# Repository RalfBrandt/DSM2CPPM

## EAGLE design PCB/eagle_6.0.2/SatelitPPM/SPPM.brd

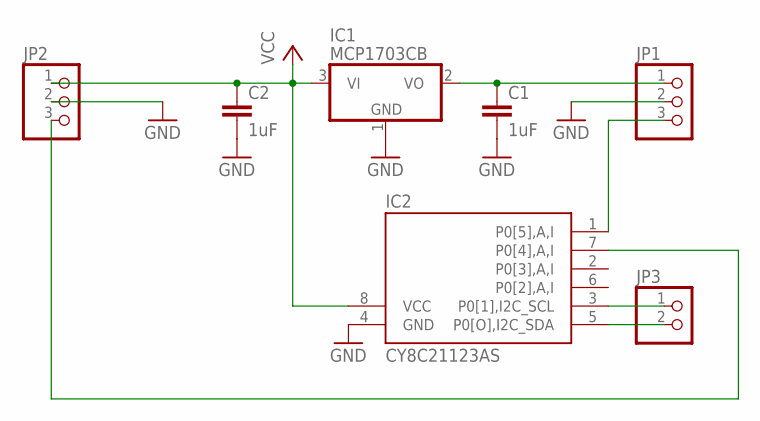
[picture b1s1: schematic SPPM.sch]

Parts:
C1, C2: 1uF; C0805
IC1: MCP1703CB; SOT23
IC2: CY8C21123AS; SOIC8
JP1, JP2: PINHD-1X3; 1X03
JP3: PINHD-1X2; 1X02

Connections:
GND: C1.2, C2.2, IC1.1 (GND), IC2.4 (GND), JP1.2, JP2.2
unnamed: IC2.7 (P0[4],A,I), JP2.3
unnamed: C1.1, IC1.2 (VO), JP1.1
unnamed: IC2.5 (P0[O],I2C_SDA), JP3.2
unnamed: IC2.3 (P0[1],I2C_SCL), JP3.1
unnamed: IC2.1 (P0[5],A,I), JP1.3
VCC: C2.1, IC1.3 (VI), IC2.8 (VCC), JP2.1

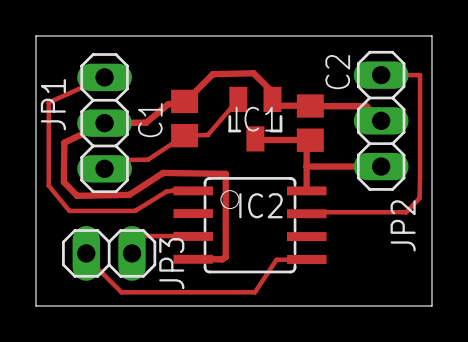
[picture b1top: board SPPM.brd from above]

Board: 2 copper layers, 22.0 x 15.0 mm, 7 parts (0 on the bottom side), 7 nets.

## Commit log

2016-10-21 :boom::camel: Added .gitattributes & .gitignore files
2016-10-21 Initial upload
    Convert a Spektrum satelite serial date to CPPM (Sum PPM)
2016-10-21 Add CAD files
2017-10-09 Update V8
    FIXed that 10bit is 2048 where as 2ms-1ms is 1000us
